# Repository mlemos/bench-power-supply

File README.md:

#Fonte de Alimentação para Bancada#

Este é o projeto de uma fonte linear para bancada. É uma fonte bem simples utilizando um regulador LM317 e que pode fornecer tensões entre 3 e 15 Volts com corrente máxima de até 1A.

##Dicas para Montagem##

No diagrama você não verá alguns componentes importantes da fonte, pois usei o diagrama do Eagle para montar a placa de circuito impresso com alguns conectores para componentes que ficaram fora da placa. Neste caso você verá, no diagrama e na placa, os conectores para a ligação destes componentes.

Fiz isto pois pretendo montar a fonte numa caixa de projetos para que fique bem profissional. Veja na foto uma versão quase final do projeto.

Os componentes que ficam de foram sõa:

* Transformador AC 127 para 12+12 2A
* Potenciômetro 5K ohms
* Regulador de tensão LM317
* LED indicador de funcionamento
* Bourne de saída (um vermelho e um preto)

Outro cuidado fundamental é o de colocar um belo dissipador de calor no LM317. Não sei direito como dimensionar este componente, coloquei o maior que consegui encontrar e que dava para ser montado na traseira da caixa que estou usando na montagem.

##E mais...##

Na foto você verá que estou montando duas fontes e colocando na mesma caixa.

E também coloquei coisas como uma chave geral para ligar e desligar a alimentação da rede.

E uma chave para cada fonte que corta a saída da fonte. Assim você pode cortar a alimentação de cada fonte individualmente.

E também adicionei dois medidores digitais de corrente e tensão.

Por enquanto é isto... espero que gostem!

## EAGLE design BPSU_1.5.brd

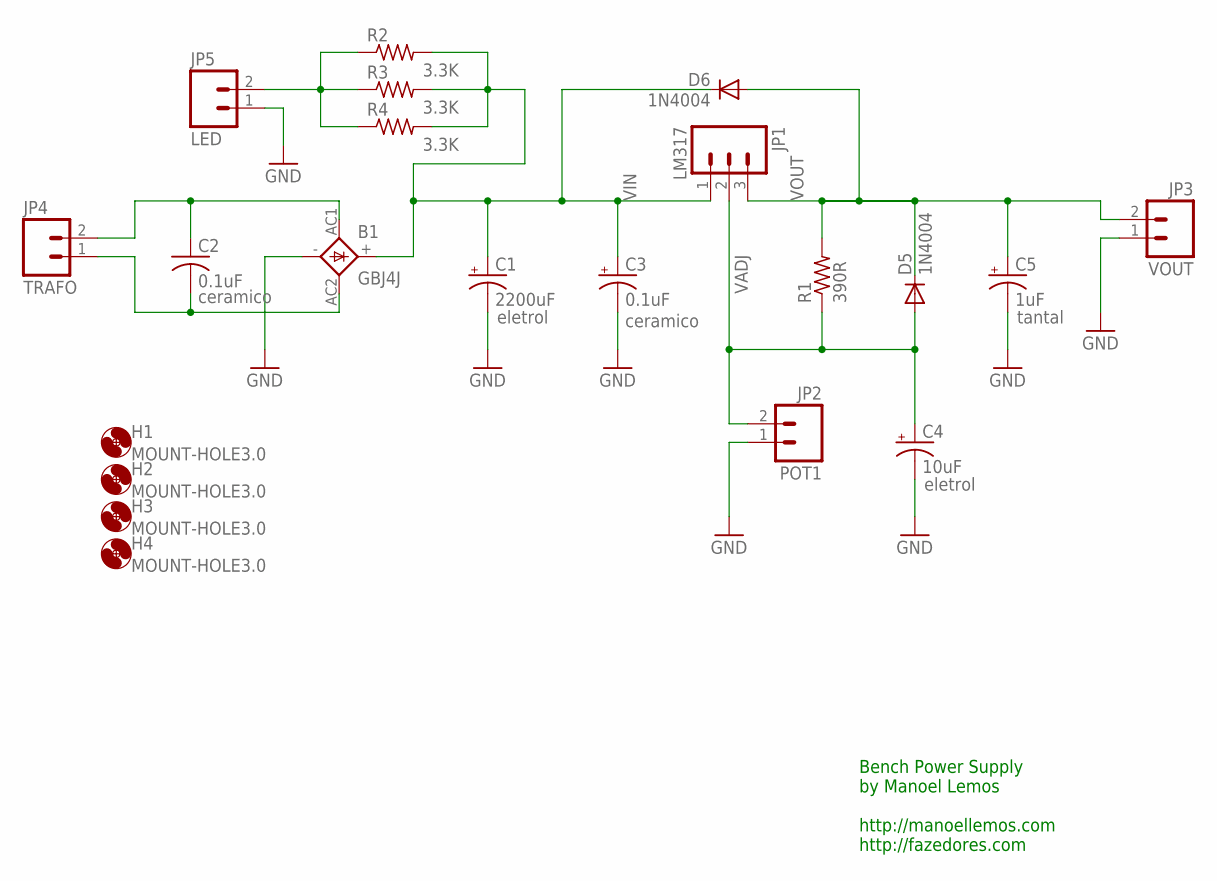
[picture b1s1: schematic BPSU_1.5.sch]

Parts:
B1: GBJ4J; GBJ
C1: 2200uF; E7,5-18
C2: 0.1uF; C075-063X106
C3: 0.1uF; E3,5-8
C4: 10uF; E3,5-8
C5: 1uF; E3,5-8
D5, D6: 1N4004; DO41-10
H1, H2, H3, H4: MOUNT-HOLE3.0; 3,0
JP1: LM317; 1X03_LONGPADS
JP2: POT1; 1X02_LONGPADS_ML
JP3: VOUT; 1X02_LONGPADS_ML
JP4: TRAFO; 1X02_LONGPADS_ML
JP5: LED; 1X02_LONGPADS_ML
R1: 390R; 0204/7
R2, R3, R4: 3.3K; 0204/7

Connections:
GND: B1.-, C1.-, C3.-, C4.-, C5.-, JP2.1, JP3.1, JP5.1
unnamed: JP5.2, R2.1, R3.1, R4.1
unnamed: B1.AC1, C2.1, JP4.2
unnamed: B1.AC2, C2.2, JP4.1
VADJ: C4.+, D5.A, JP1.2, JP2.2, R1.1
VIN: B1.+, C1.+, C3.+, D6.C, JP1.1, R2.2, R3.2, R4.2
VOUT: C5.+, D5.C, D6.A, JP1.3, JP3.2, R1.2

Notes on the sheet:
eletrol
ceramico
tantal
Bench Power Supply by Manoel Lemos http://manoellemos.com http://fazedores.com

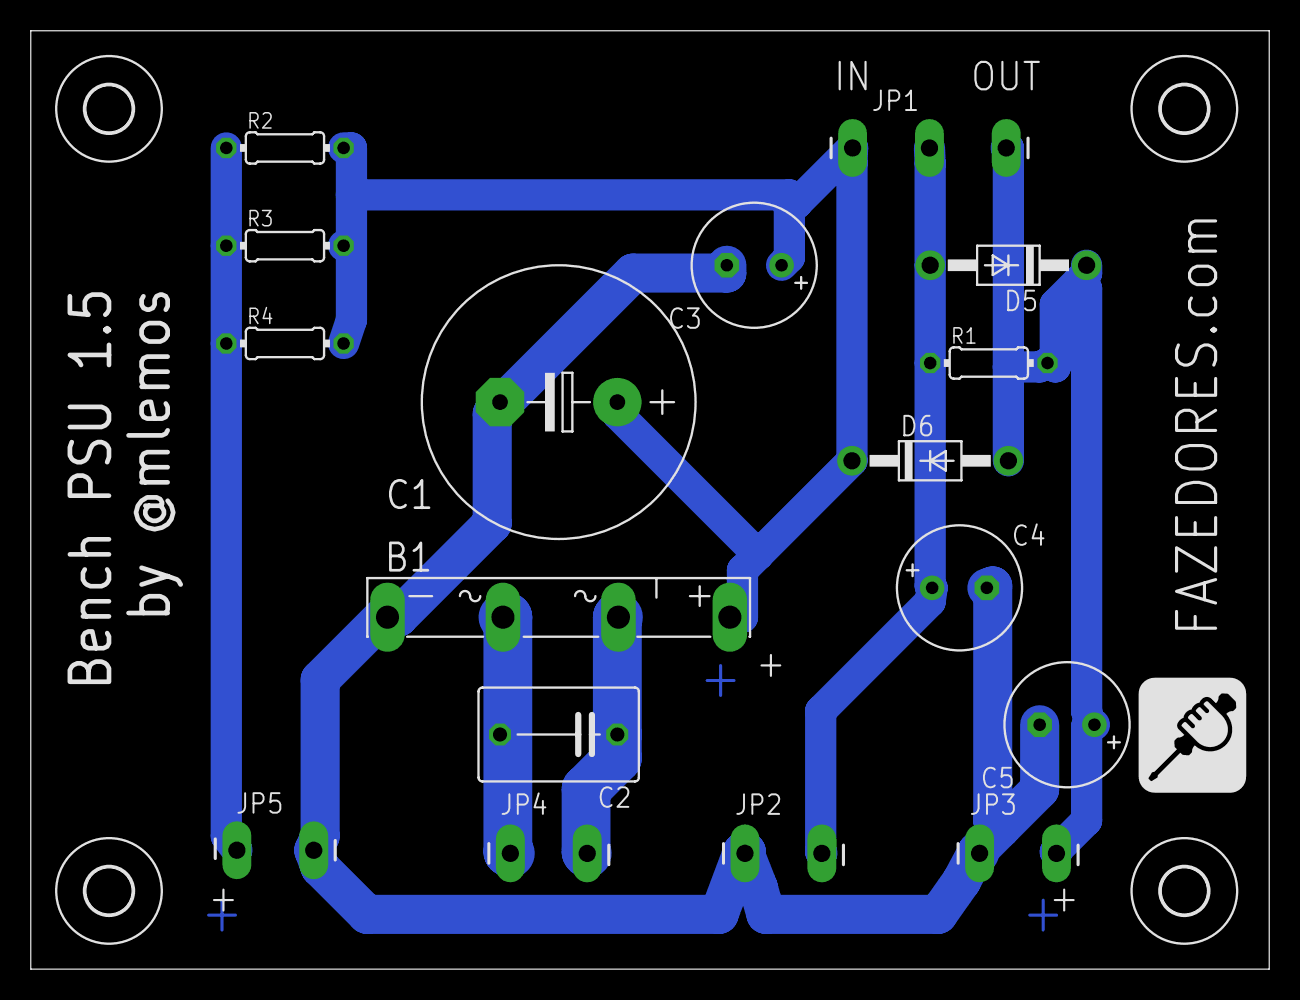
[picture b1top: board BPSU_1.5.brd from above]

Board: 2 copper layers, 80.4 x 61.0 mm, 22 parts (0 on the bottom side), 7 nets.

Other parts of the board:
U$5: LOGO_FAZEDORES_BIG_TSILK

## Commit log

2014-06-12 primeiro commit
2014-06-12 Mensagem inicial do readme.
2014-06-12 Adicionando os aquivos do Eagle!
2014-06-12 Melhorias no readme.

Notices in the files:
parts and their libraries:
SparkFun-Aesthetics: Licensing: CC v3.0 Share-Alike You are welcome to use this library for commercial purposes.
